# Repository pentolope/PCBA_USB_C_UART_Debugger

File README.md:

# USB-C UART Debug Adapter

USB-C to 3.3 V UART debug adapter: bus-powered USB 2.0 Full-Speed device breaking out TX/RX/GND/3V3 and optional RTS/CTS.

This repository holds the design problem for a **USB-C to 3.3 V UART debug adapter**. The brief fixes the function and the interface contract: a bus-powered USB 2.0 Full-Speed device with a correct USB-C device-side CC network, USB ESD protection close to the connector, local decoupling, and a target-side header carrying TX, RX, GND, a 3V3 reference and optional RTS/CTS on a 0.1-inch or compact locking header. It also fixes process intent: pick a commonly available USB-UART bridge, prefer two layers, route D+/D- as a deliberate differential pair, and document whatever impedance approximation is used. The brief's own modality is carried across unchanged: RTS/CTS is offered as an option, two layers is a preference, and the benchmark-intent clauses say what the repository *should* do rather than what it must.

Everything else is the design agent's to decide. The brief names no bridge IC, no connector part, no ESD device, no board outline, no stackup numbers and no impedance target — those belong in `open_decisions`, not in this README. Where a choice is made during design it must be made and justified against cited evidence, not back-filled into the brief as if the user had asked for it.

> **This board has not been designed.** There is no schematic, no layout and no
> part selection here — only the brief, a reading of the brief, and the
> scaffolding a design run needs. That is the intended state of this repository,
> not a gap in it.

## What the brief fixes, and what it leaves open

The brief pins down 16 requirements and deliberately leaves
17 decisions to whoever designs the board. The `Source` column says
which is which: `brief` is quoted from [BRIEF.md](BRIEF.md), `metadata` comes
from the benchmark catalogue, and `open` means the brief does not fix it.

| Aspect | Value | Source |
|---|---|---|
| Product function | USB-C to 3.3 V UART debug adapter | brief |
| UART signalling level | 3.3 V | brief |
| USB interface class | USB 2.0 Full-Speed device | brief |
| Power source | Bus-powered (no separate supply input stated) | brief |
| Target-side signal set | TX, RX, GND, 3V3 reference, plus RTS/CTS as an option | brief |
| Target-side header style | 0.1-inch header or a compact locking header (the brief permits either; which one is not fixed) | brief |
| USB-C CC network | Correct device-side CC network required; no topology, value or tolerance stated | brief |
| ESD protection | USB ESD protection, placed close to the connector | brief |
| Decoupling | Local decoupling required | brief |
| Connector placement | USB and target-side connectors clearly separated | brief |
| USB-UART bridge | A commonly available bridge; no specific part named by the brief | brief |
| D+/D- routing | Deliberate differential pair; any impedance approximation must be documented | brief |
| Likely layer count | 2 (stated as a preference, not a mandate) | metadata |
| Primary stressors | USB 2.0 differential routing, ESD, USB-C CC resistors, small QFN | metadata |
| Board outline, size and mounting | Not fixed by the brief — design agent's choice | open |

The full split, with the verbatim brief text substantiating every fixed
requirement, is in [board/requirements.md](board/requirements.md) and
machine-readably in [board/requirements.json](board/requirements.json).

**Missing details are design freedom, not permission to fabricate unstated user
requirements.** A choice the brief left open is recorded as a decision, with its
reasoning — never promoted into a requirement.

## Benchmark position

| | |
|---|---|
| Benchmark id | 5 of 32 |
| Category | high-speed-lite |
| Difficulty | 2 / 5 |
| Brief detail | 3 / 5 |
| Likely layer count | 2 |
| Primary stressors | USB 2.0 differential routing, ESD, USB-C CC resistors, small QFN |

Board 05 sits in the `high-speed-lite` category at difficulty 2/5 with brief detail 3/5: an adapter of modest scope whose difficulty concentrates in doing four specific things correctly at once — USB 2.0 differential routing, ESD, the USB-C CC resistors, and a small QFN. The brief is deliberately mid-detail: it pins down the interface contract (speed class, power source, signal set, header style, protection placement) while naming no part, no dimension and no impedance number. The interesting test is the "Prefer two layers, but route D+/D- as a deliberate differential pair and document any impedance approximation" clause — it invites a controlled-impedance claim on a stackup that may not be able to guarantee one, and rewards an agent that documents the approximation honestly rather than asserting a number.

This repository is one of thirty-two. The suite, the protocol and the results
live in [PCBA_AutoDesignAndTest_Bench](https://github.com/pentolope/PCBA_AutoDesignAndTest_Bench).

## Repository layout

| Path | Contents |
|---|---|
| `BRIEF.md` | the supplied brief — authoritative, preserved byte for byte, never edited |
| `board/requirements.md` | what the brief fixes, what it leaves open, and where decisions get recorded |
| `board/requirements.json` | the same split, machine-readable, each fixed requirement bound to brief text |
| `board/manifest.template.json` | the toolkit's minimum manifest, pre-filled for this board |
| `board/toolchain.json` | where this board's build finds KiCad and the router |
| `benchmark/metadata.json` | the supplied catalogue entry — category, difficulty, detail, stressors |
| `docs/architecture.md` | the decisions this board must make, as questions, unanswered |
| `docs/sources.md` | the classes of evidence the design will have to cite |
| `docs/status.md` | what exists, what does not, and what is deliberately absent |
| `candidates/` | disposable search output, ignored by Git |
| `.claude/skills/` | the accountability-review skill [CLAUDE.md](CLAUDE.md) requires before a push |
| `tooling/PCBA_AutoDesignAndTest` | the shared verification/routing/release toolkit, as a pinned submodule |

## Getting the repository

The toolkit is a submodule and carries KiCad Routing Tools as a submodule of its
own, so clone recursively:

```bash
git clone --recursive https://github.com/pentolope/PCBA_USB_C_UART_Debugger.git
```

```bash
git submodule update --init --recursive
```

## Designing the board

Generic verification, routing and release logic is **not** written here. It is
consumed from `tooling/PCBA_AutoDesignAndTest`, which is board-agnostic by
construction and must stay that way; this repository owns the board and nothing
else. Start from
[the toolkit's onboarding guide](tooling/PCBA_AutoDesignAndTest/examples/onboarding.md),
and see [CLAUDE.md](CLAUDE.md) for the rules a design run works under.

```bash
python3 tooling/PCBA_AutoDesignAndTest/run.py preflight
```

## Brief integrity

`BRIEF.md` SHA-256 `0c5897542317b8fdc90d1251febe01efa33c86589f59024910c426d053b9a461`

Every quotation in `board/requirements.json` is bound to those exact bytes. If
the brief ever changes, the bindings are stale by construction — which is the
point of recording the digest.

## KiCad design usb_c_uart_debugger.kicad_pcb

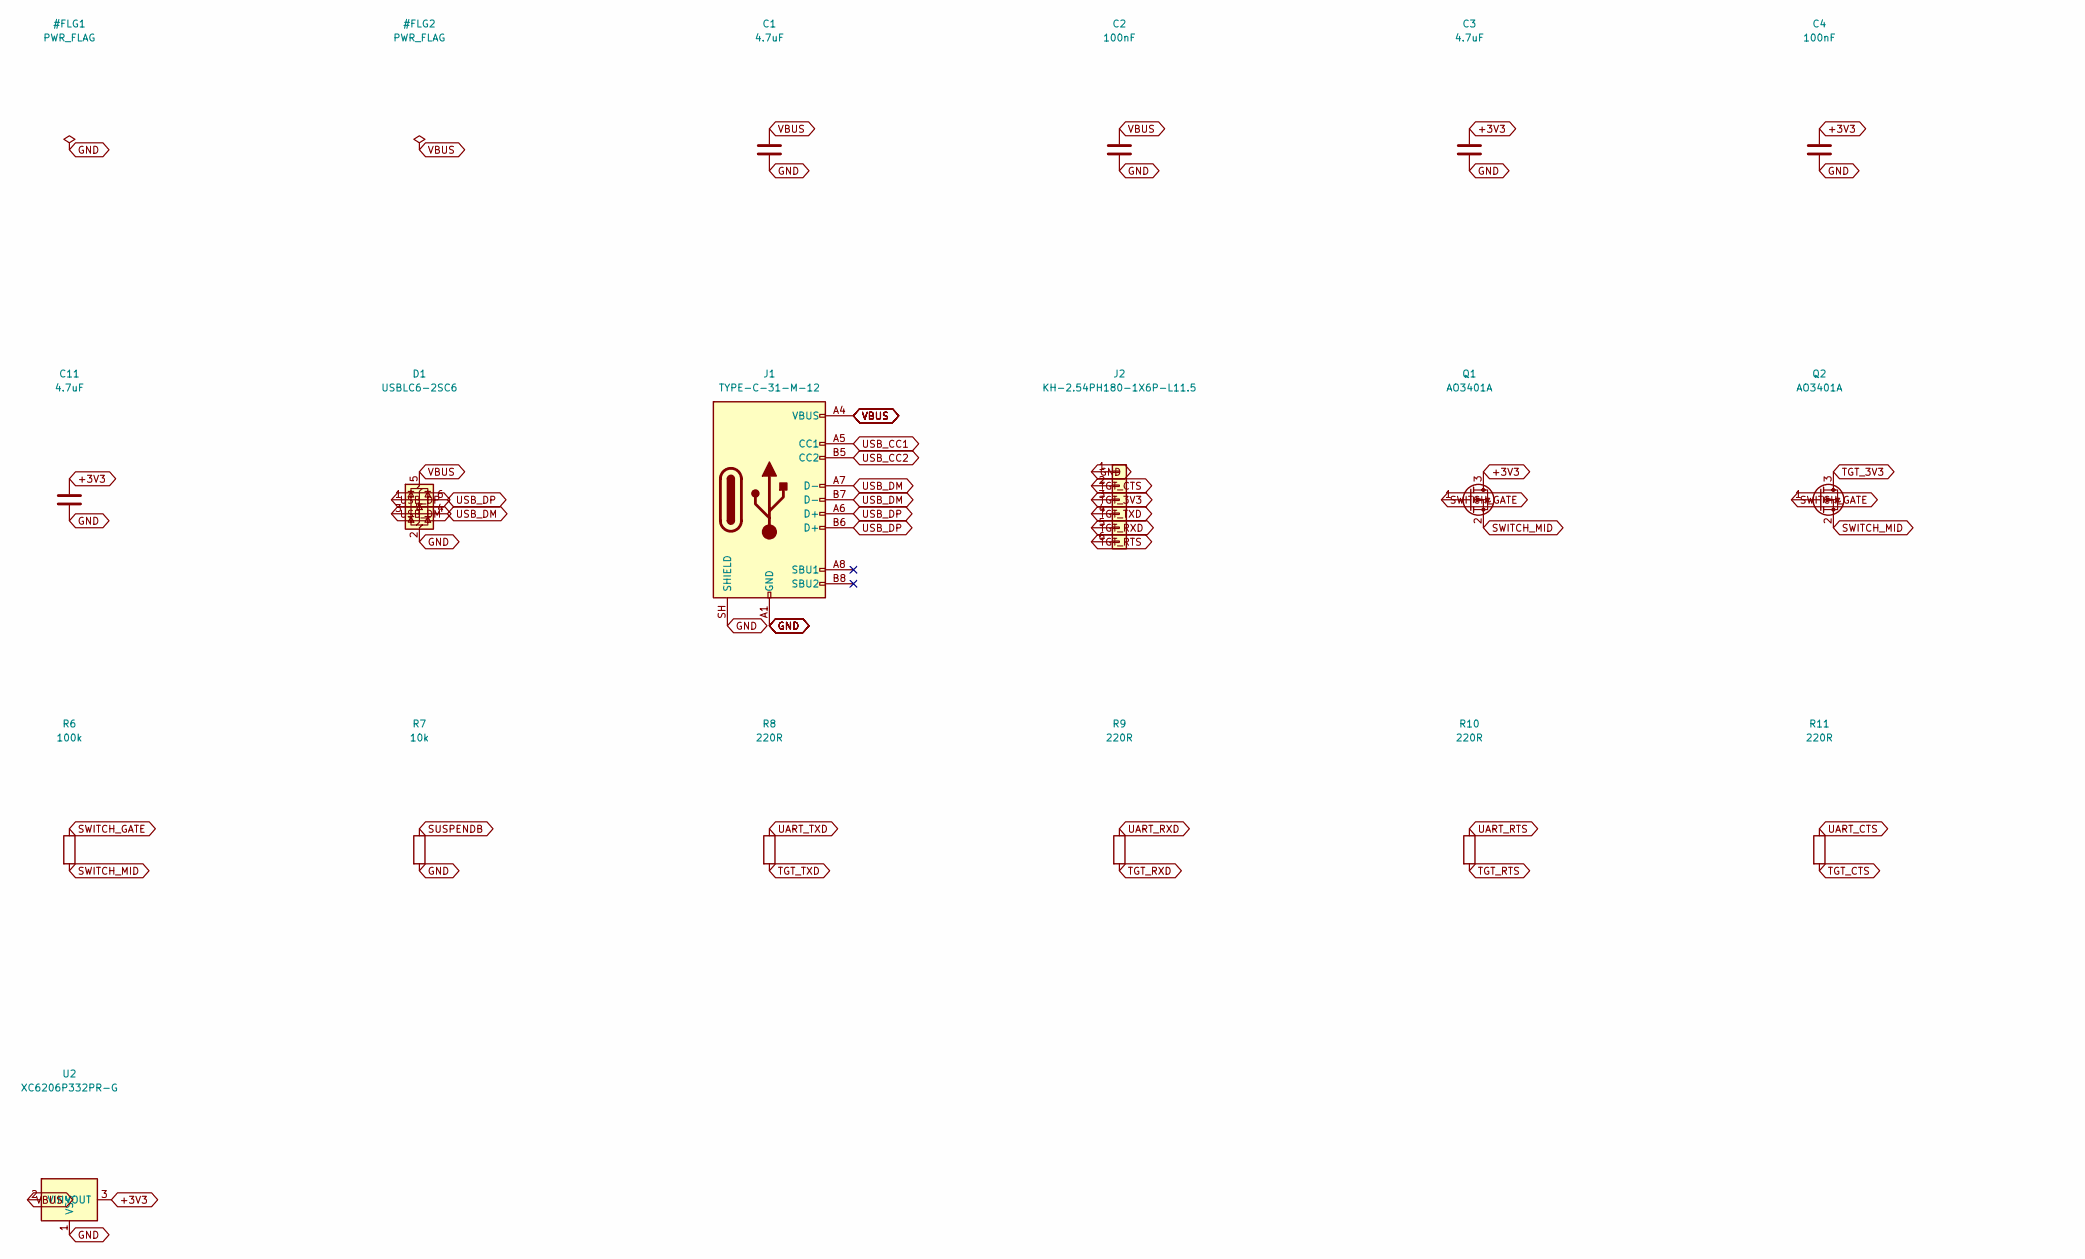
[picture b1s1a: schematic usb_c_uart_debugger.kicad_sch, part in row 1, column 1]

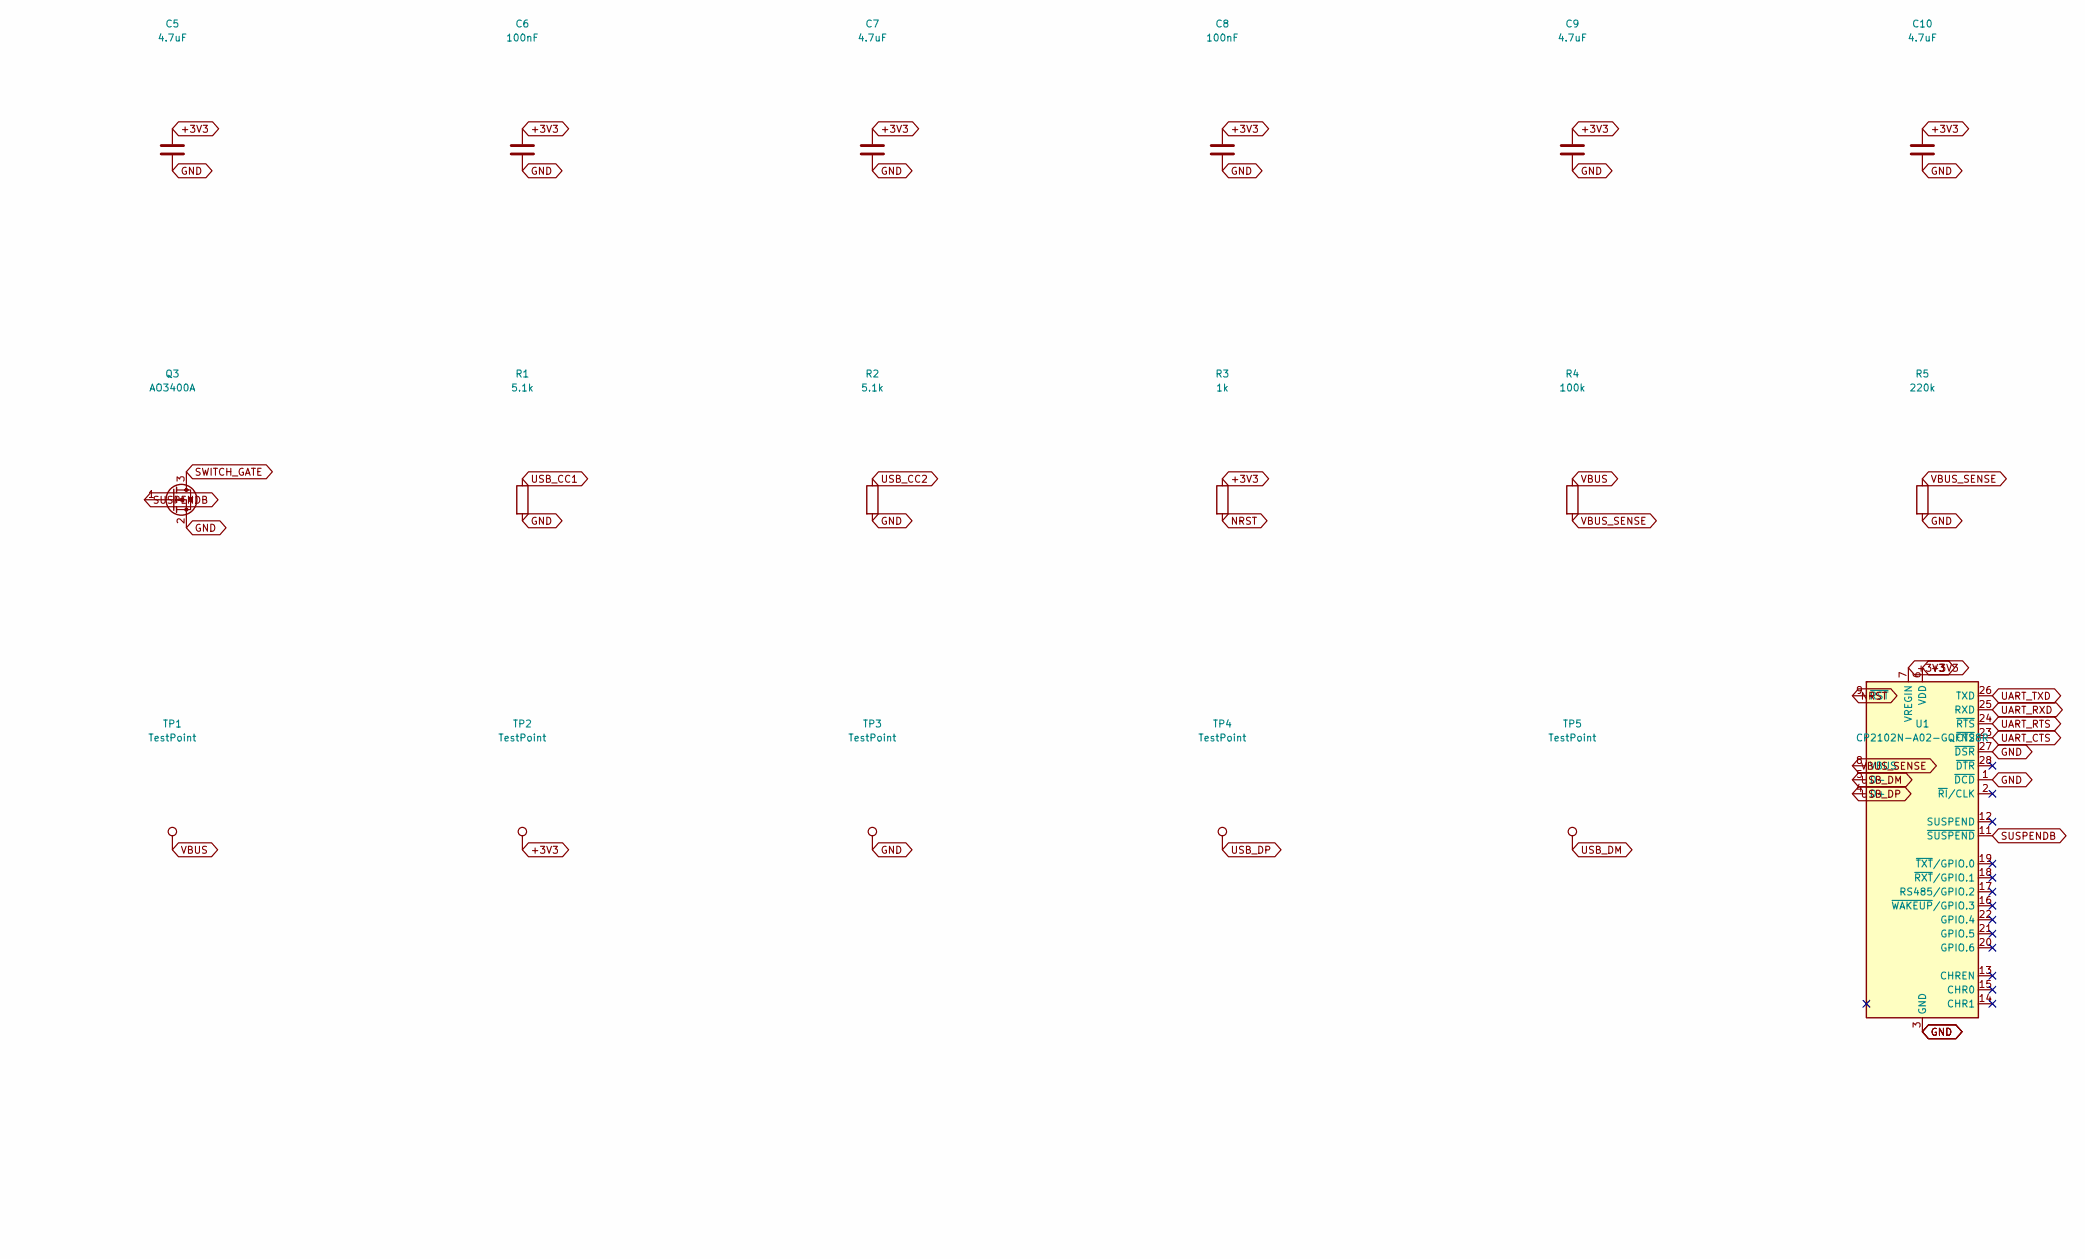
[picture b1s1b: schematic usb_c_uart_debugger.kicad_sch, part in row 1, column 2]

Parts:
C1, C3, C5, C7, C9, C10, C11: 4.7uF; C_0603_1608Metric; MPN CL10A475KO8NNNC; LCSC C19666
C2, C4, C6, C8: 100nF; C_0603_1608Metric; MPN CC0603KRX7R9BB104; LCSC C14663
D1: USBLC6-2SC6; SOT-23-6; MPN USBLC6-2SC6; LCSC C7519
J1: TYPE-C-31-M-12; USB_C_Receptacle_HRO_TYPE-C-31-M-12; MPN TYPE-C-31-M-12; LCSC C165948
J2: KH-2.54PH180-1X6P-L11.5; PinHeader_1x06_P2.54mm_Vertical; MPN KH-2.54PH180-1X6P-L11.5; LCSC C2905486
Q1, Q2: AO3401A; SOT-23; MPN AO3401A; LCSC C15127
Q3: AO3400A; SOT-23; MPN AO3400A; LCSC C20917
R1, R2: 5.1k; R_0603_1608Metric; MPN 0603WAF5101T5E; LCSC C23186
R3: 1k; R_0603_1608Metric; MPN 0603WAF1001T5E; LCSC C21190
R4, R6: 100k; R_0603_1608Metric; MPN 0603WAF1003T5E; LCSC C25803
R5: 220k; R_0603_1608Metric; MPN 0603WAF2203T5E; LCSC C22961
R7: 10k; R_0603_1608Metric; MPN 0603WAF1002T5E; LCSC C25804
R8, R9, R10, R11: 220R; R_0603_1608Metric; MPN 0603WAF2200T5E; LCSC C22962
TP1, TP2, TP3, TP4, TP5: TestPoint; TestPoint_Pad_D1.0mm
U1: CP2102N-A02-GQFN28R; QFN-28-1EP_5x5mm_P0.5mm_CP2102N; MPN CP2102N-A02-GQFN28R; LCSC C964632
U2: XC6206P332PR-G; SOT-89-3; MPN XC6206P332PR-G; LCSC C526275

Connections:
+3V3: C3.1, C4.1, C5.1, C6.1, C7.1, C8.1, C9.1, C10.1, C11.1, Q1.3 (D), R3.1, TP2.1, U1.6 (VDD), U1.7 (VREGIN), U2.3 (VOUT)
GND: C1.2, C2.2, C3.2, C4.2, C5.2, C6.2, C7.2, C8.2, C9.2, C10.2, C11.2, D1.2 (GND), J1.A1 (GND), J1.A12 (GND), J1.B1 (GND), J1.B12 (GND), J1.SH (SHIELD), J2.1, Q3.2 (S), R1.2, R2.2, R5.2, R7.2, TP3.1, U1.1 (~DCD), U1.3 (GND), U1.27 (~DSR), U1.29 (GND), U2.1 (VSS)
NRST: R3.2, U1.9 (~RST)
SUSPENDB: Q3.1 (G), R7.1, U1.11 (~SUSPEND)
SWITCH_GATE: Q1.1 (G), Q2.1 (G), Q3.3 (D), R6.1
SWITCH_MID: Q1.2 (S), Q2.2 (S), R6.2
TGT_3V3: J2.3, Q2.3 (D)
TGT_CTS: J2.2, R11.2
TGT_RTS: J2.6, R10.2
TGT_RXD: J2.5, R9.2
TGT_TXD: J2.4, R8.2
UART_CTS: R11.1, U1.23 (~CTS)
UART_RTS: R10.1, U1.24 (~RTS)
UART_RXD: R9.1, U1.25 (RXD)
UART_TXD: R8.1, U1.26 (TXD)
USB_CC1: J1.A5 (CC1), R1.1
USB_CC2: J1.B5 (CC2), R2.1
USB_DM: D1.3 (I/O2), D1.4 (I/O2), J1.A7 (D-), J1.B7 (D-), TP5.1, U1.5 (D-)
USB_DP: D1.1 (I/O1), D1.6 (I/O1), J1.A6 (D+), J1.B6 (D+), TP4.1, U1.4 (D+)
VBUS: C1.1, C2.1, D1.5 (VBUS), J1.A4 (VBUS), J1.A9 (VBUS), J1.B4 (VBUS), J1.B9 (VBUS), R4.1, TP1.1, U2.2 (VIN)
VBUS_SENSE: R4.2, R5.1, U1.8 (VBUS)

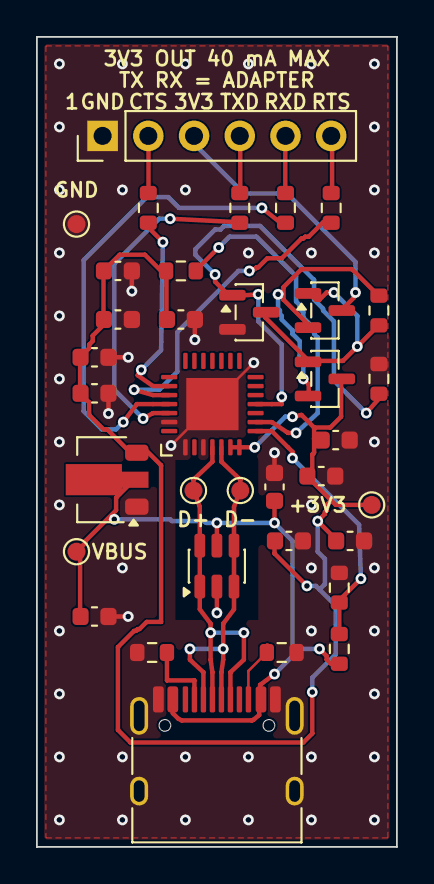
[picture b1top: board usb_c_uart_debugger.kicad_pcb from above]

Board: 2 copper layers, 20.0 x 45.0 mm, 35 parts (0 on the bottom side), 21 nets.

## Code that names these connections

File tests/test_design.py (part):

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                                 netlist.TYPE_C_RD_TOLERANCE)

    def test_the_data_lines_pass_through_the_suppressor(self):
        for net, pins in (("USB_DP", ("1", "6")), ("USB_DM", ("3", "4"))):
            for pin in pins:
                self.assertEqual(self.mapping["D1." + pin], net)
        self.assertEqual(self.mapping["D1.2"], "GND")
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        self.assertEqual(mapping["Q1.2"], mapping["Q2.2"])
        self.assertEqual(mapping["Q1.1"], mapping["Q2.1"])
        self.assertEqual(mapping["Q1.3"], "+3V3")
        self.assertEqual(mapping["Q2.3"], "TGT_3V3")

    def test_the_switch_is_driven_from_the_suspend_output(self):
        mapping = netlist.pin_to_net()
        self.assertEqual(mapping["U1." + netlist.BRIDGE_PINS["SUSPENDB"]],
                         mapping["Q3.1"])
        self.assertEqual(mapping["Q3.2"], "GND")
        self.assertEqual(mapping["Q3.3"], mapping["Q1.1"])
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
